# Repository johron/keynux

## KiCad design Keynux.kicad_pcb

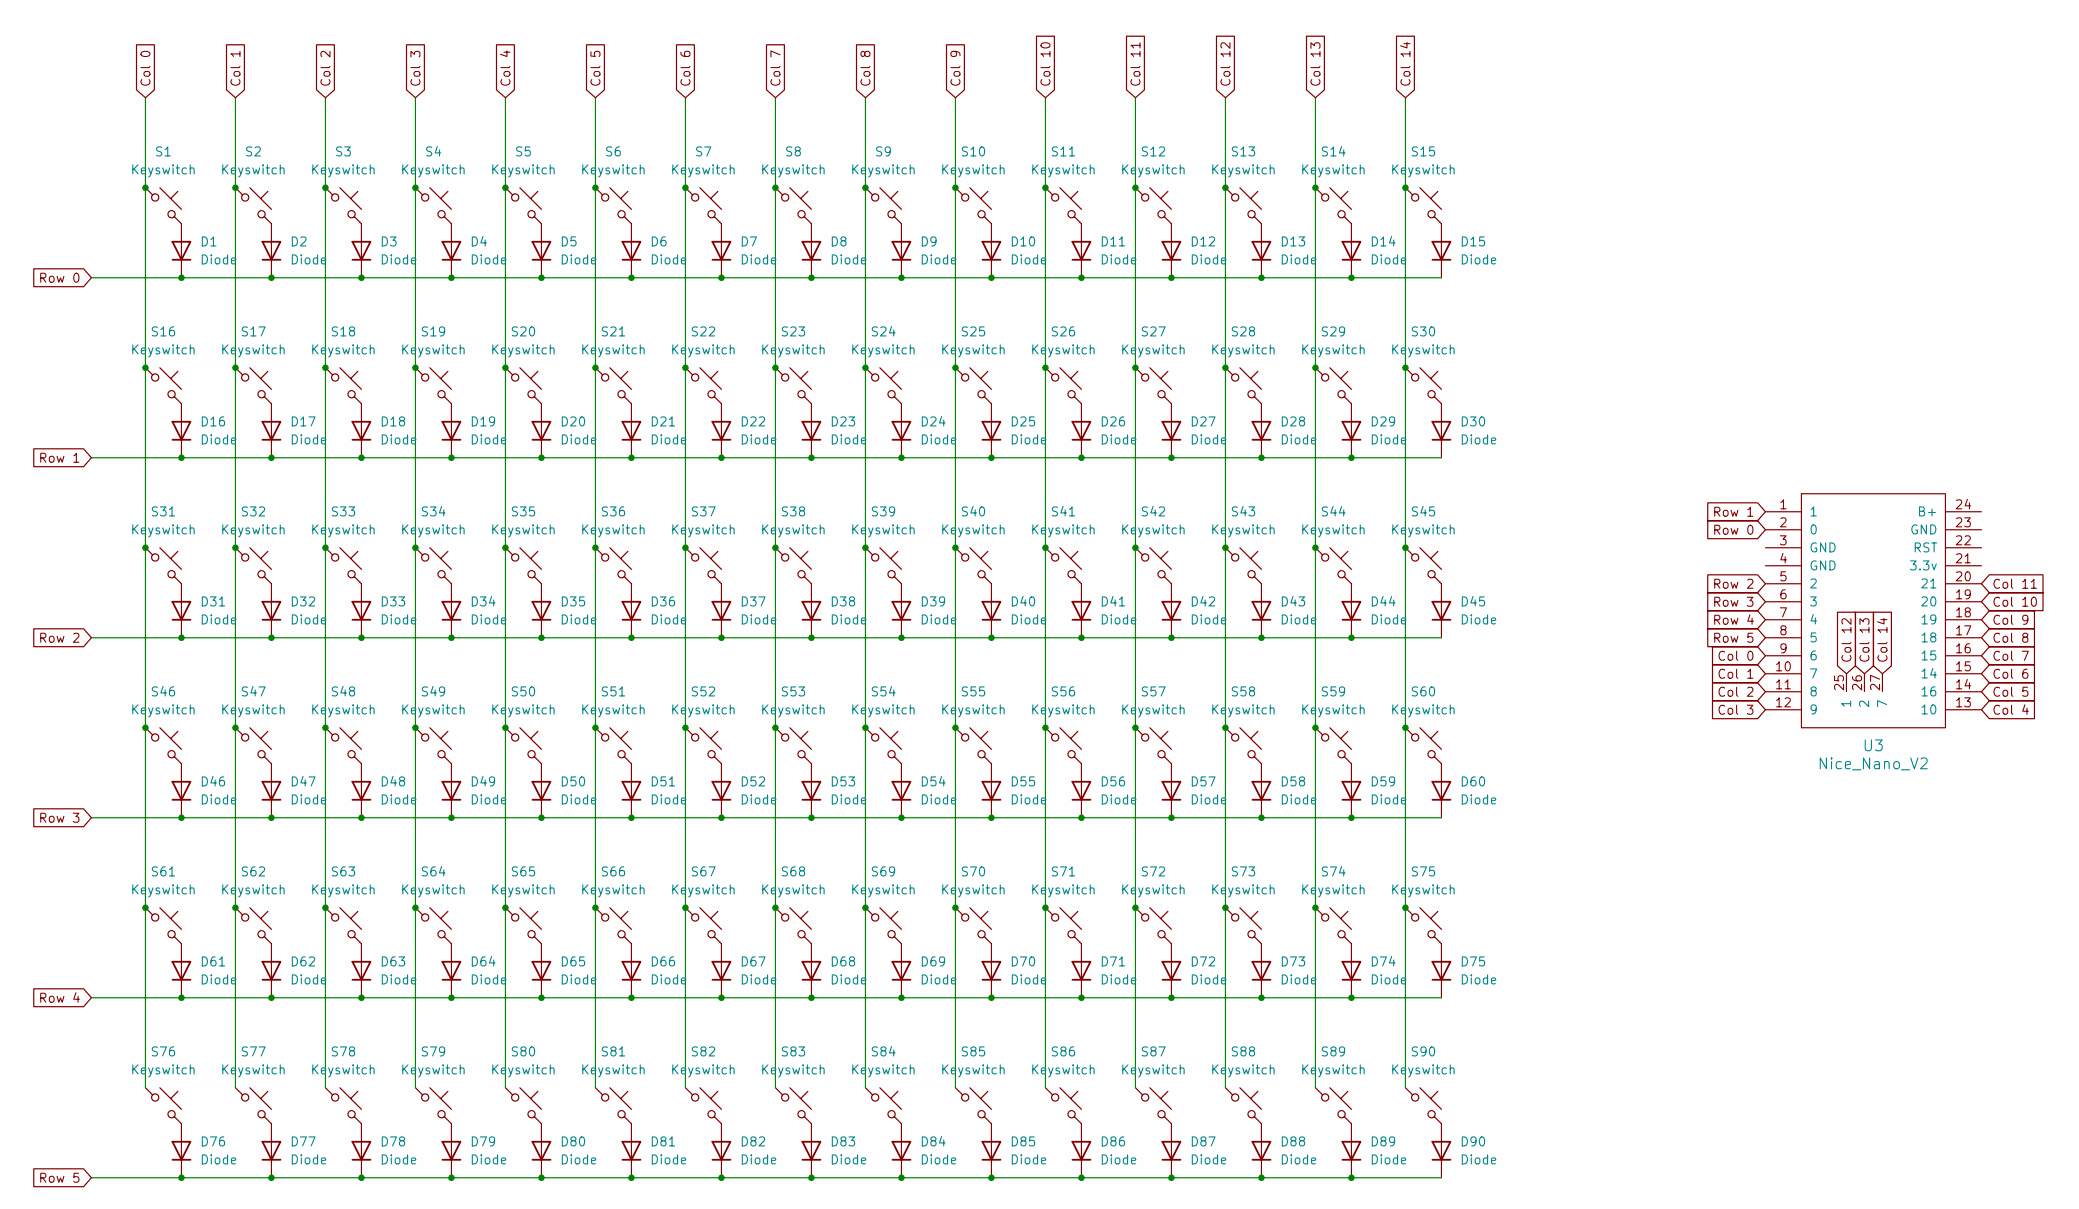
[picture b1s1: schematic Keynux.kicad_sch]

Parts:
D1, D2, D3, D4, D5, D6, D7, D8, D9, D10, D11, D12, D13, D14, D15, D16, D17, D18, D19, D20, D21, D22, D23, D24, D25, D26, D27, D28, D29, D30, D31, D32, D33, D34, D35, D36, D37, D38, D39, D40, D41, D42, D43, D44, D45, D46, D47, D48, D49, D50, D51, D52, D53, D54, D55, D56, D57, D58, D59, D60, D61, D62, D63, D64, D65, D66, D67, D68, D69, D70, D71, D72, D73, D74, D75, D76, D77, D78, D79, D80, D81, D82, D83, D84, D85, D86, D87, D88, D89, D90: Diode; Diode_DO-35
S1, S2, S3, S4, S5, S6, S7, S8, S9, S10, S11, S12, S13, S14, S15, S16, S17, S18, S19, S20, S21, S22, S23, S24, S25, S26, S27, S28, S29, S30, S31, S32, S33, S34, S35, S36, S37, S38, S39, S40, S41, S42, S43, S44, S45, S46, S47, S48, S49, S50, S51, S52, S53, S54, S55, S56, S57, S58, S59, S60, S61, S62, S63, S64, S65, S66, S67, S68, S69, S70, S71, S72, S73, S74, S75, S76, S77, S78, S79, S80, S81, S82, S83, S84, S85, S86, S87, S88, S89, S90: Keyswitch; Hotswap_MX_1.00u
U3: Nice_Nano_V2

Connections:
Col 0: S1.1, S16.1, S31.1, S46.1, S61.1, S76.1, U3.9 (6)
Col 1: S2.1, S17.1, S32.1, S47.1, S62.1, S77.1, U3.10 (7)
Col 2: S3.1, S18.1, S33.1, S48.1, S63.1, S78.1, U3.11 (8)
Col 3: S4.1, S19.1, S34.1, S49.1, S64.1, S79.1, U3.12 (9)
Col 4: S5.1, S20.1, S35.1, S50.1, S65.1, S80.1, U3.13 (10)
Col 5: S6.1, S21.1, S36.1, S51.1, S66.1, S81.1, U3.14 (16)
Col 6: S7.1, S22.1, S37.1, S52.1, S67.1, S82.1, U3.15 (14)
Col 7: S8.1, S23.1, S38.1, S53.1, S68.1, S83.1, U3.16 (15)
Col 8: S9.1, S24.1, S39.1, S54.1, S69.1, S84.1, U3.17 (18)
Col 9: S10.1, S25.1, S40.1, S55.1, S70.1, S85.1, U3.18 (19)
Col 10: S11.1, S26.1, S41.1, S56.1, S71.1, S86.1, U3.19 (20)
Col 11: S12.1, S27.1, S42.1, S57.1, S72.1, S87.1, U3.20 (21)
Col 12: S13.1, S28.1, S43.1, S58.1, S73.1, S88.1, U3.25 (1)
Col 13: S14.1, S29.1, S44.1, S59.1, S74.1, S89.1, U3.26 (2)
Col 14: S15.1, S30.1, S45.1, S60.1, S75.1, S90.1, U3.27 (7)
unnamed: D1.2 (A), S1.2
unnamed: D2.2 (A), S2.2
unnamed: D3.2 (A), S3.2
unnamed: D4.2 (A), S4.2
unnamed: D5.2 (A), S5.2
unnamed: D6.2 (A), S6.2
unnamed: D7.2 (A), S7.2
unnamed: D8.2 (A), S8.2
unnamed: D9.2 (A), S9.2
unnamed: D10.2 (A), S10.2
unnamed: D11.2 (A), S11.2
unnamed: D12.2 (A), S12.2
unnamed: D13.2 (A), S13.2
unnamed: D14.2 (A), S14.2
unnamed: D15.2 (A), S15.2
unnamed: D16.2 (A), S16.2
unnamed: D17.2 (A), S17.2
unnamed: D18.2 (A), S18.2
unnamed: D19.2 (A), S19.2
unnamed: D20.2 (A), S20.2
unnamed: D21.2 (A), S21.2
unnamed: D22.2 (A), S22.2
unnamed: D23.2 (A), S23.2
unnamed: D24.2 (A), S24.2
unnamed: D25.2 (A), S25.2
unnamed: D26.2 (A), S26.2
unnamed: D27.2 (A), S27.2
unnamed: D28.2 (A), S28.2
unnamed: D29.2 (A), S29.2
unnamed: D30.2 (A), S30.2
unnamed: D31.2 (A), S31.2
unnamed: D32.2 (A), S32.2
unnamed: D33.2 (A), S33.2
unnamed: D34.2 (A), S34.2
unnamed: D35.2 (A), S35.2
unnamed: D36.2 (A), S36.2
unnamed: D37.2 (A), S37.2
unnamed: D38.2 (A), S38.2
unnamed: D39.2 (A), S39.2
unnamed: D40.2 (A), S40.2
unnamed: D41.2 (A), S41.2
unnamed: D42.2 (A), S42.2
unnamed: D43.2 (A), S43.2
unnamed: D44.2 (A), S44.2
unnamed: D45.2 (A), S45.2
unnamed: D46.2 (A), S46.2
unnamed: D47.2 (A), S47.2
unnamed: D48.2 (A), S48.2
unnamed: D49.2 (A), S49.2
unnamed: D50.2 (A), S50.2
unnamed: D51.2 (A), S51.2
unnamed: D52.2 (A), S52.2
unnamed: D53.2 (A), S53.2
unnamed: D54.2 (A), S54.2
unnamed: D55.2 (A), S55.2
unnamed: D56.2 (A), S56.2
unnamed: D57.2 (A), S57.2
unnamed: D58.2 (A), S58.2
unnamed: D59.2 (A), S59.2
unnamed: D60.2 (A), S60.2
unnamed: D61.2 (A), S61.2
unnamed: D62.2 (A), S62.2
unnamed: D63.2 (A), S63.2
unnamed: D64.2 (A), S64.2
unnamed: D65.2 (A), S65.2
unnamed: D66.2 (A), S66.2
unnamed: D67.2 (A), S67.2
unnamed: D68.2 (A), S68.2
unnamed: D69.2 (A), S69.2
unnamed: D70.2 (A), S70.2
unnamed: D71.2 (A), S71.2
unnamed: D72.2 (A), S72.2
unnamed: D73.2 (A), S73.2
unnamed: D74.2 (A), S74.2
unnamed: D75.2 (A), S75.2
unnamed: D76.2 (A), S76.2
unnamed: D77.2 (A), S77.2
unnamed: D78.2 (A), S78.2
unnamed: D79.2 (A), S79.2
unnamed: D80.2 (A), S80.2
unnamed: D81.2 (A), S81.2
unnamed: D82.2 (A), S82.2
unnamed: D83.2 (A), S83.2
unnamed: D84.2 (A), S84.2
unnamed: D85.2 (A), S85.2
unnamed: D86.2 (A), S86.2
unnamed: D87.2 (A), S87.2
unnamed: D88.2 (A), S88.2
unnamed: D89.2 (A), S89.2
unnamed: D90.2 (A), S90.2
Row 0: D1.1 (K), D2.1 (K), D3.1 (K), D4.1 (K), D5.1 (K), D6.1 (K), D7.1 (K), D8.1 (K), D9.1 (K), D10.1 (K), D11.1 (K), D12.1 (K), D13.1 (K), D14.1 (K), D15.1 (K), U3.2 (0)
Row 1: D16.1 (K), D17.1 (K), D18.1 (K), D19.1 (K), D20.1 (K), D21.1 (K), D22.1 (K), D23.1 (K), D24.1 (K), D25.1 (K), D26.1 (K), D27.1 (K), D28.1 (K), D29.1 (K), D30.1 (K), U3.1
Row 2: D31.1 (K), D32.1 (K), D33.1 (K), D34.1 (K), D35.1 (K), D36.1 (K), D37.1 (K), D38.1 (K), D39.1 (K), D40.1 (K), D41.1 (K), D42.1 (K), D43.1 (K), D44.1 (K), D45.1 (K), U3.5 (2)
Row 3: D46.1 (K), D47.1 (K), D48.1 (K), D49.1 (K), D50.1 (K), D51.1 (K), D52.1 (K), D53.1 (K), D54.1 (K), D55.1 (K), D56.1 (K), D57.1 (K), D58.1 (K), D59.1 (K), D60.1 (K), U3.6 (3)
Row 4: D61.1 (K), D62.1 (K), D63.1 (K), D64.1 (K), D65.1 (K), D66.1 (K), D67.1 (K), D68.1 (K), D69.1 (K), D70.1 (K), D71.1 (K), D72.1 (K), D73.1 (K), D74.1 (K), D75.1 (K), U3.7 (4)
Row 5: D76.1 (K), D77.1 (K), D78.1 (K), D79.1 (K), D80.1 (K), D81.1 (K), D82.1 (K), D83.1 (K), D84.1 (K), D85.1 (K), D86.1 (K), D87.1 (K), D88.1 (K), D89.1 (K), D90.1 (K), U3.8 (5)

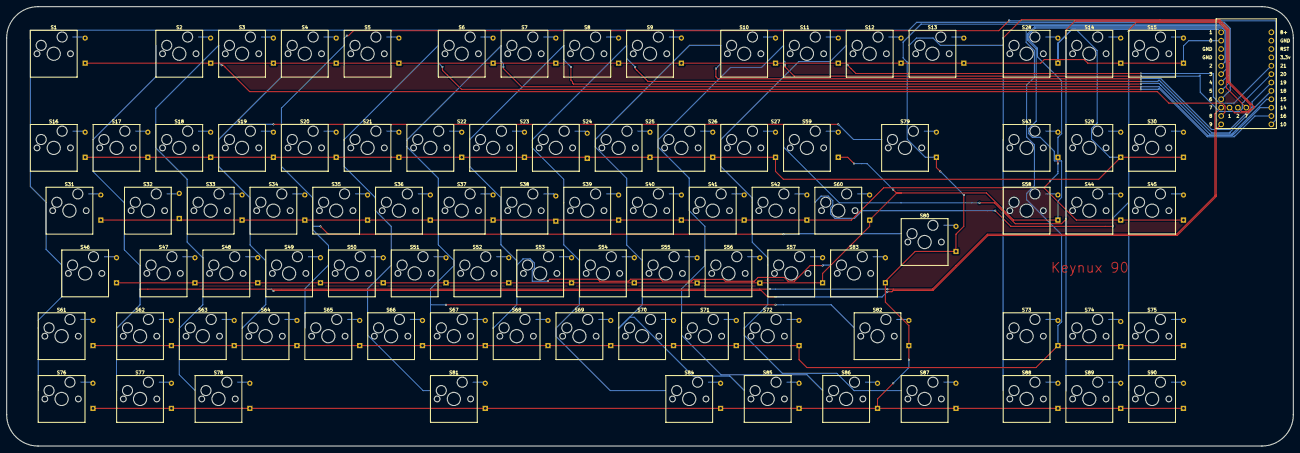
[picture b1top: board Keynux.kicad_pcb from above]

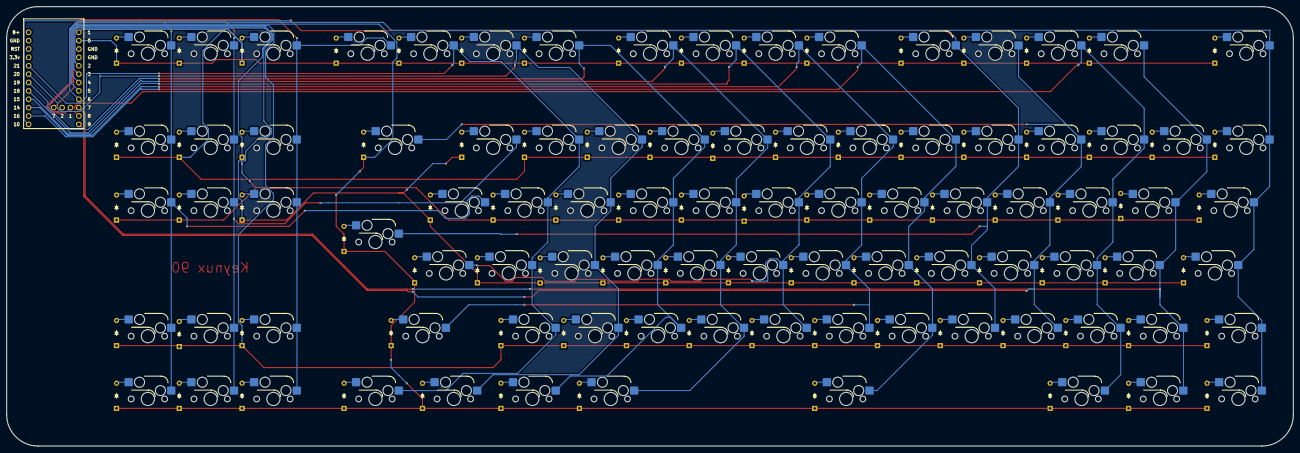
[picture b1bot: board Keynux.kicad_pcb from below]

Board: 2 copper layers, 390.5 x 133.4 mm, 181 parts (90 on the bottom side), 111 nets.

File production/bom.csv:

Designator,Footprint,Quantity,Value,LCSC Part #
"D1, D10, D11, D12, D13, D14, D15, D16, D17, D18, D19, D2, D20, D21, D22, D23, D24, D25, D26, D27, D28, D29, D3, D30, D31, D32, D33, D34, D35, D36, D37, D38, D39, D4, D40, D41, D42, D43, D44, D45, D46, D47, D48, D49, D5, D50, D51, D52, D53, D54, D55, D56, D57, D58, D59, D6, D60, D61, D62, D63, D64, D65, D66, D67, D68, D69, D7, D70, D71, D72, D73, D74, D75, D76, D77, D78, D79, D8, D80, D81, D82, D83, D84, D85, D86, D87, D88, D89, D9, D90",Diode_DO-35,90,Diode,
"S1, S10, S11, S12, S13, S14, S15, S16, S17, S18, S19, S2, S20, S21, S22, S23, S24, S25, S26, S27, S28, S29, S3, S30, S31, S32, S33, S34, S35, S36, S37, S38, S39, S4, S40, S41, S42, S43, S44, S45, S46, S47, S48, S49, S5, S50, S51, S52, S53, S54, S55, S56, S57, S58, S59, S6, S60, S61, S62, S63, S64, S65, S66, S67, S68, S69, S7, S70, S71, S72, S73, S74, S75, S76, S77, S78, S79, S8, S80, S81, S82, S83, S84, S85, S86, S87, S88, S89, S9, S90",Hotswap_MX_1.00u,90,Keyswitch,
U3,Nice_Nano_V2,1,Nice_Nano_V2,

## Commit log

2025-06-04 init
2025-06-05 connected everything, now connect to mc
2025-06-05 save
